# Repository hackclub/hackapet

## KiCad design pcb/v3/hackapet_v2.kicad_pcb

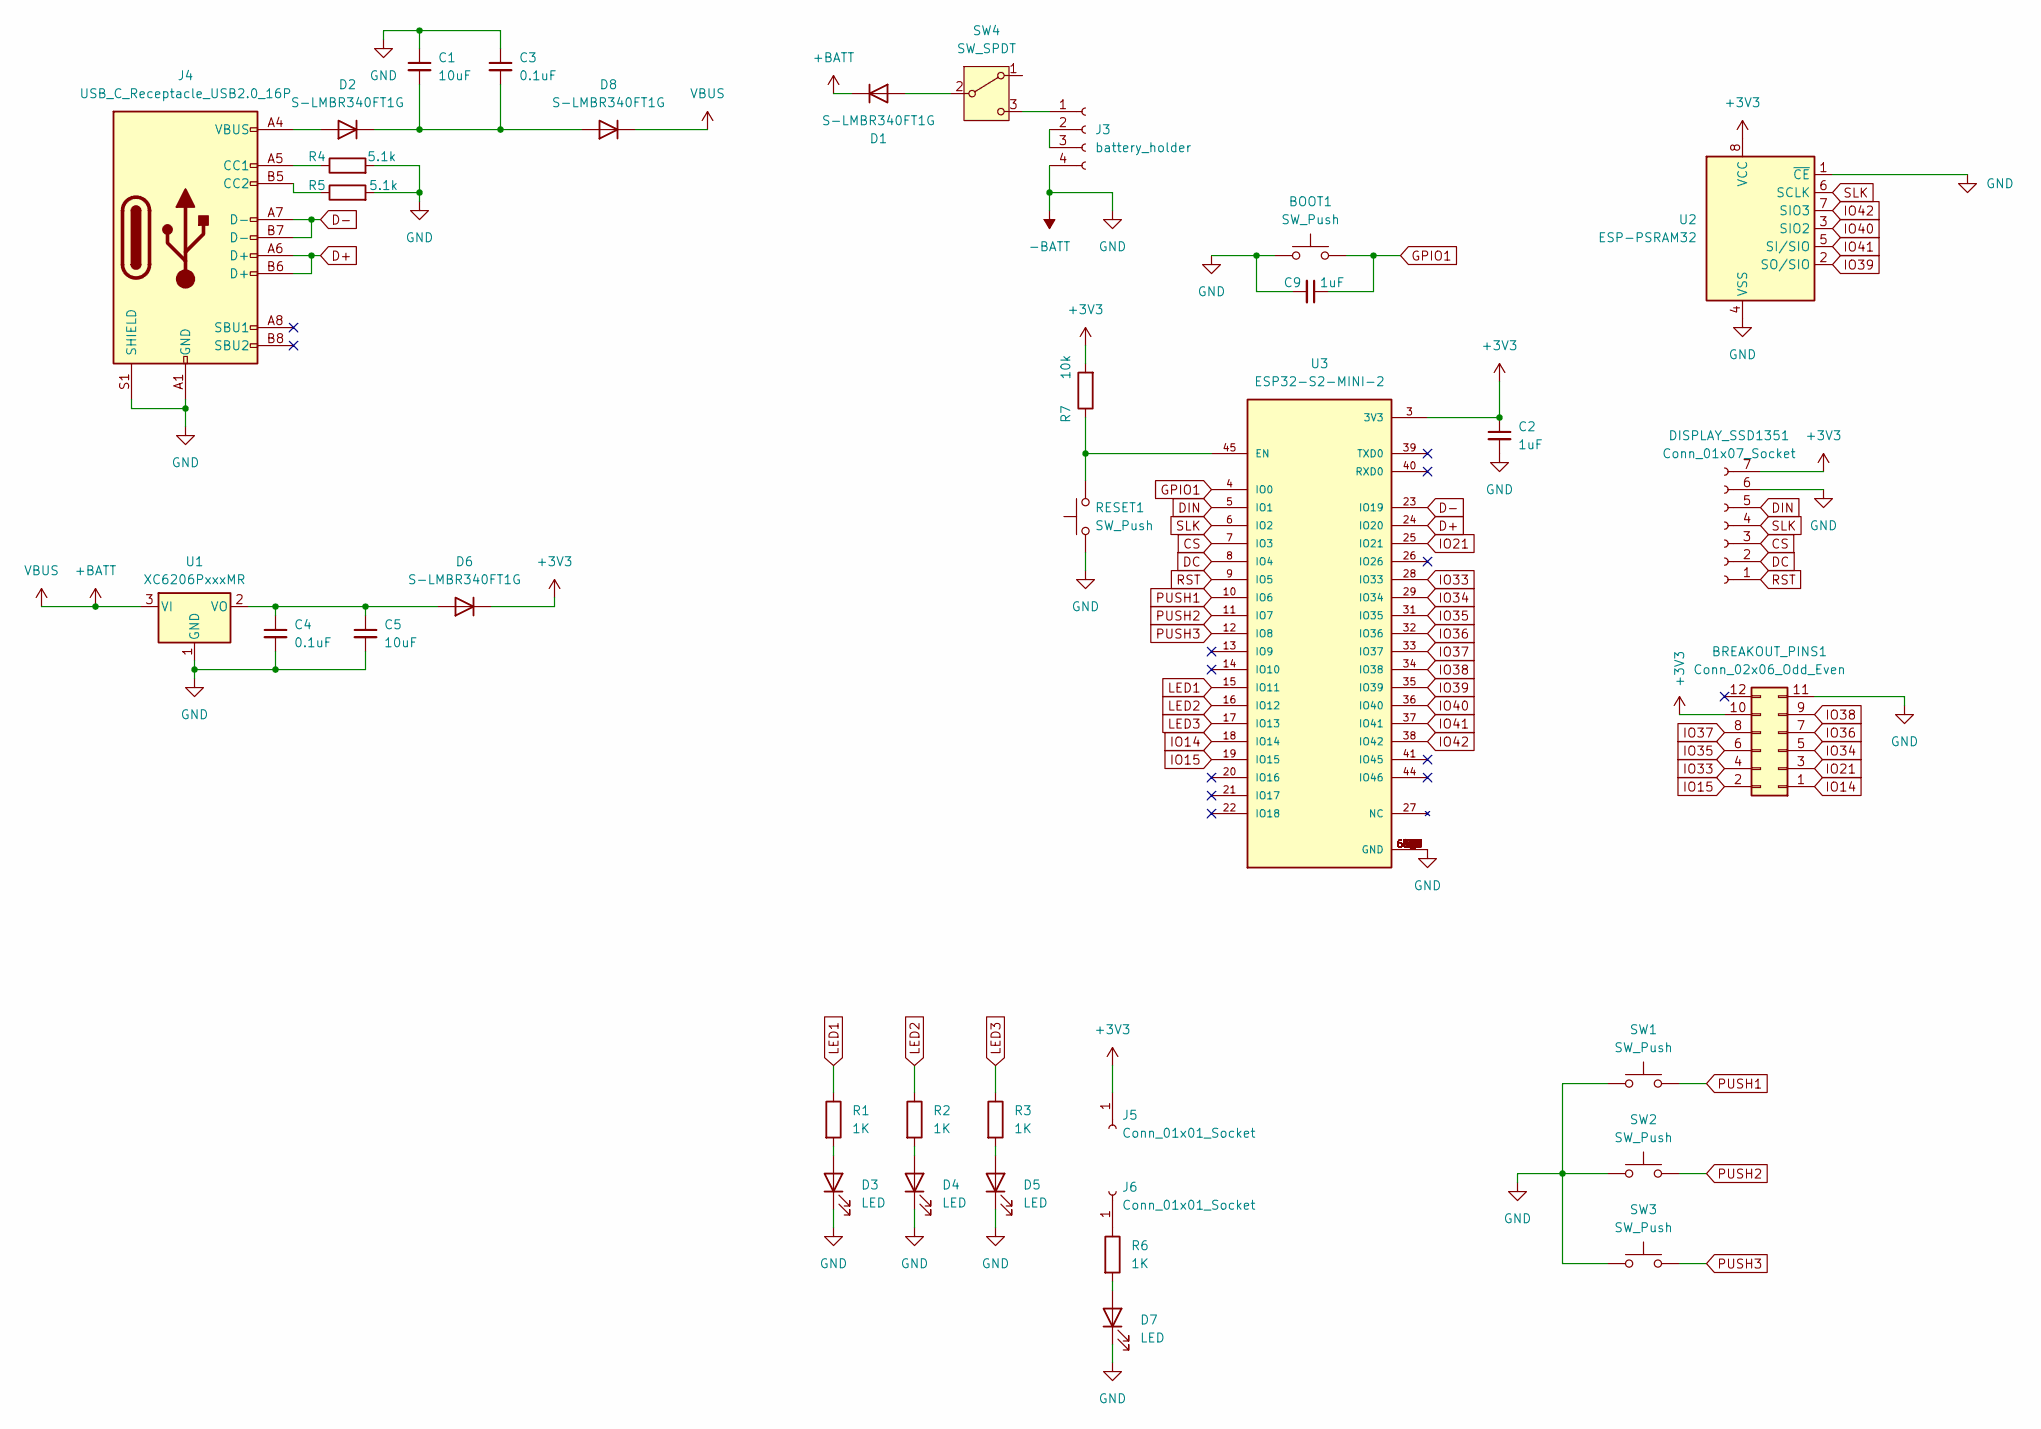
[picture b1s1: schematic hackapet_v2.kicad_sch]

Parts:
BOOT1: SW_Push; SW_Push_1P1T_XKB_TS-1187A; LCSC C381038
BREAKOUT_PINS1: Conn_02x06_Odd_Even
C1, C5: 10uF; C_0805_2012Metric; LCSC C5189822
C2, C9: 1uF; C_0805_2012Metric; LCSC C215803
C3, C4: 0.1uF; C_0805_2012Metric; LCSC C28378
D1, D2, D6, D8: S-LMBR340FT1G; D_0805_2012Metric; LCSC C2972823
D3, D4, D5, D7: LED; LED_0805_2012Metric
DISPLAY_SSD1351: Conn_01x07_Socket; PinSocket_1x07_P2.54mm_Vertical; LCSC C22438073
J3: battery_holder; 1022_batteryholder
J4: USB_C_Receptacle_USB2.0_16P; USB_C_Receptacle_HCTL_HC-TYPE-C-16P-01A; LCSC C393939
J5, J6: Conn_01x01_Socket; PinSocket_1x01_P2.54mm_Vertical
R1, R2, R3, R6: 1K; R_0805_2012Metric; LCSC C17513
R4, R5: 5.1k; R_0805_2012Metric; LCSC C104375
R7: 10k; R_0402_1005Metric
RESET1: SW_Push; SW_Push_1P1T_XKB_TS-1187A
SW1, SW2, SW3: SW_Push; SW_Push_1P1T_NO_6x6mm_H9.5mm; LCSC C381038
SW4: SW_SPDT; SW_DPDT_CK_JS202011JCQN; LCSC C221666
U1: XC6206PxxxMR; SOT-23-3
U2: ESP-PSRAM32; SOIC-8_3.9x4.9mm_P1.27mm
U3: ESP32-S2-MINI-2; XCVR_ESP32-S2-MINI-1; PARTREV 1.0; LCSC C3013906

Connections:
+3V3: BREAKOUT_PINS1.10, C2.1, D6.1 (K), DISPLAY_SSD1351.7, J5.1, R7.2, U2.8 (VCC), U3.3 (3V3)
+BATT: D1.1 (K), D8.1 (K), U1.3 (VI)
-BATT: BOOT1.1, BREAKOUT_PINS1.11, C1.1, C2.2, C3.1, C4.2, C5.2, C9.2, D3.1 (K), D4.1 (K), D5.1 (K), D7.1 (K), DISPLAY_SSD1351.6, J3.4, J4.A1 (GND), J4.A12 (GND), J4.B1 (GND), J4.B12 (GND), J4.S1 (SHIELD), R4.2, R5.2, RESET1.1, SW1.1, SW2.1, SW3.1, U1.1 (GND), U2.1 (~CE), U2.4 (VSS), U3.1 (GND), U3.2 (GND), U3.30 (GND), U3.42 (GND), U3.43 (GND), U3.46 (GND), U3.47 (GND), U3.48 (GND), U3.49 (GND), U3.50 (GND), U3.51 (GND), U3.52 (GND), U3.53 (GND), U3.54 (GND), U3.55 (GND), U3.56 (GND), U3.57 (GND), U3.58 (GND), U3.59 (GND), U3.60 (GND), U3.61 (GND), U3.61_1 (GND), U3.61_2 (GND), U3.61_3 (GND), U3.61_4 (GND), U3.61_5 (GND), U3.61_6 (GND), U3.61_7 (GND), U3.61_8 (GND), U3.62 (GND), U3.63 (GND), U3.64 (GND), U3.65 (GND)
CS: DISPLAY_SSD1351.3, U3.7 (IO3)
D+: J4.A6 (D+), J4.B6 (D+), U3.24 (IO20)
D-: J4.A7 (D-), J4.B7 (D-), U3.23 (IO19)
DC: DISPLAY_SSD1351.2, U3.8 (IO4)
DIN: DISPLAY_SSD1351.5, U3.5 (IO1)
GPIO1: BOOT1.2, C9.1, U3.4 (IO0)
IO14: BREAKOUT_PINS1.1, U3.18 (IO14)
IO15: BREAKOUT_PINS1.2, U3.19 (IO15)
IO21: BREAKOUT_PINS1.3, U3.25 (IO21)
IO33: BREAKOUT_PINS1.4, U3.28 (IO33)
IO34: BREAKOUT_PINS1.5, U3.29 (IO34)
IO35: BREAKOUT_PINS1.6, U3.31 (IO35)
IO36: BREAKOUT_PINS1.7, U3.32 (IO36)
IO37: BREAKOUT_PINS1.8, U3.33 (IO37)
IO38: BREAKOUT_PINS1.9, U3.34 (IO38)
IO39: U2.2 (SO/SIO), U3.35 (IO39)
IO40: U2.3 (SIO2), U3.36 (IO40)
IO41: U2.5 (SI/SIO), U3.37 (IO41)
IO42: U2.7 (SIO3), U3.38 (IO42)
LED1: R1.1, U3.15 (IO11)
LED2: R2.1, U3.16 (IO12)
LED3: R3.1, U3.17 (IO13)
unnamed: D1.2 (A), SW4.2 (B)
unnamed: D2.2 (A), J4.A4 (VBUS), J4.A9 (VBUS), J4.B4 (VBUS), J4.B9 (VBUS)
unnamed: C1.2, C3.2, D2.1 (K), D8.2 (A)
unnamed: D3.2 (A), R1.2
unnamed: D4.2 (A), R2.2
unnamed: D5.2 (A), R3.2
unnamed: C4.1, C5.1, D6.2 (A), U1.2 (VO)
unnamed: D7.2 (A), R6.2
unnamed: J3.1, SW4.3 (C)
unnamed: J3.2, J3.3
unnamed: J4.A5 (CC1), R4.1
unnamed: J4.B5 (CC2), R5.1
unnamed: J6.1, R6.1
unnamed: R7.1, RESET1.2, U3.45 (EN)
PUSH1: SW1.2, U3.10 (IO6)
PUSH2: SW2.2, U3.11 (IO7)
PUSH3: SW3.2, U3.12 (IO8)
RST: DISPLAY_SSD1351.1, U3.9 (IO5)
SLK: DISPLAY_SSD1351.4, U2.6 (SCLK), U3.6 (IO2)

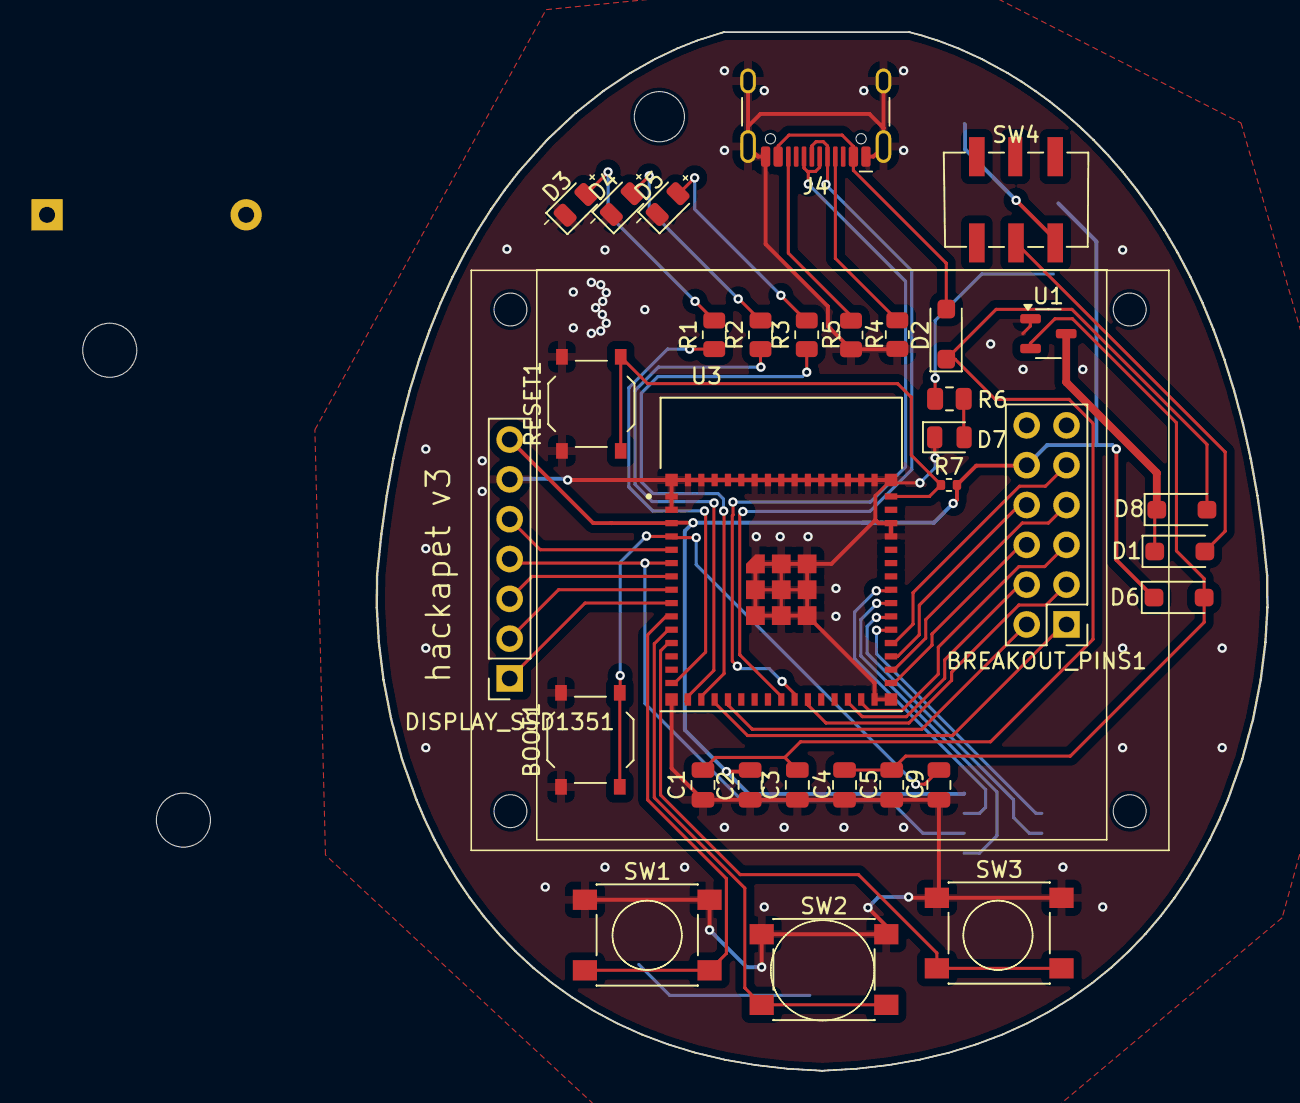
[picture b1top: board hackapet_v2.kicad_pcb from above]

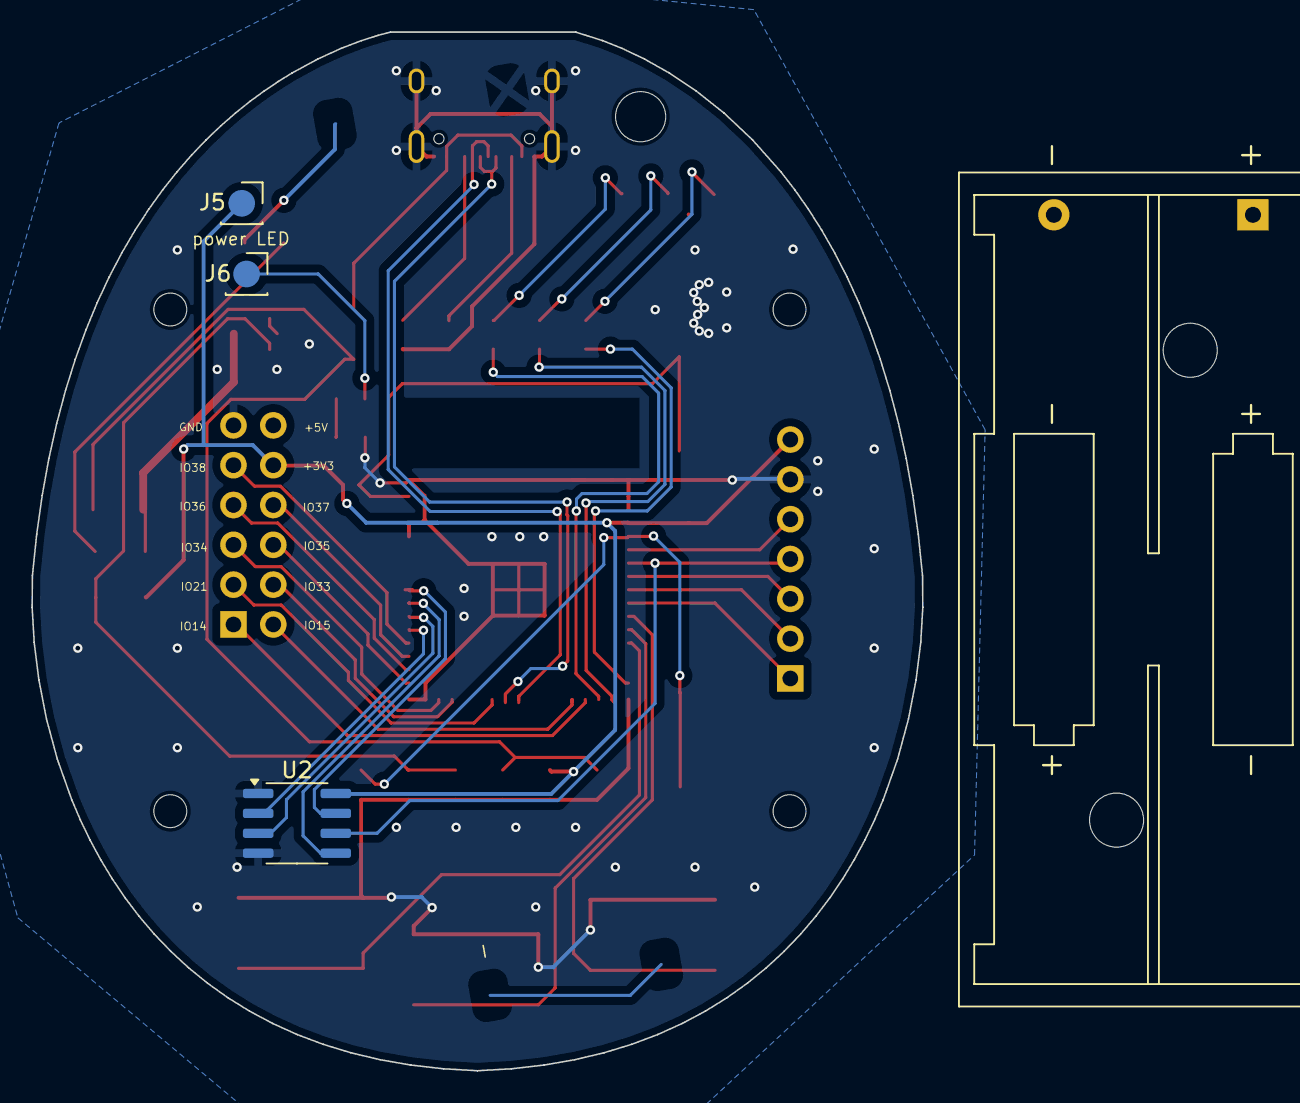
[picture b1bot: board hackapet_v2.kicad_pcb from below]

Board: 2 copper layers, 56.8 x 66.2 mm, 36 parts (4 on the bottom side), 43 nets.

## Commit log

2025-01-06 👻 boopet
2025-01-06 👻 boopet update 1
2025-01-11 feat: add my pet
2025-01-18 Added Escape The Rain! etr.srihari
2025-01-18 Update EmailButton.jsx to show email text
    Default email text color is white which makes it invisible when paired with the white bg.
2025-01-24 Adding monkey🐵
2025-01-24 adding monkey 🐵
2025-01-24 add requirments.txt
2025-01-27 ETR - UPDATE
2025-01-31 Made it work with circuit python
2025-02-01 I updated it again
2025-02-01 Added KawaiiPet
2025-02-02 starting
2025-02-02 i promise ill work more on it
2025-02-02 Create a
2025-02-02 added the main filesc lets see
2025-02-02 finished game !!!
2025-02-02 added game
2025-02-02 Create e
2025-02-03 Wizard pet - ian
    my hackapet submission
2025-02-03 new file: pets/NinjaRunner/Over.bmp new file: pets/NinjaRunner/ReadMe.md new file: pets/NinjaRunner/background.bmp new file: pets/NinjaRunner/background2.bmp new file: pets/NinjaRunner/cloud.bmp new 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
2025-02-03 Made a README
2025-02-03 Create code
2025-02-03 added my silly lil dino game
2025-02-04 space game :3
2025-02-04 silly dog eats things
    slack username - Nili
2025-02-04 wizard game
2025-02-04 added jack's adventure
    Niko slack username
2025-02-04 add cemetery crawler !
2025-02-04 add files
2025-02-04 remove pycache
2025-02-04 Add files via upload
    added some sprite changes and added idle animation + for jump
2025-02-04 just get rid of the text, adds more suspense to the game since you dont know if you are taking enough care or not
2025-02-05 hopefully good
2025-02-05 added README with button instructions
2025-02-06 silly dog eats things!
    i didn't upload the code to the right place at first lol - nili
2025-02-06 silly_dog
    i think this is it? i hope this works
2025-02-06 pls work
2025-02-08 VirtualPet
2025-02-09 Add files via upload
    god please let this work
2025-02-09 Add files via upload
    okay why do things keep on getting pulled out... this should be it?
2025-02-10 added aseprite file and made changes to the art to make it more distinct from the ref
2025-02-14 Revert "add my wys demake"
2025-02-15 final commit
2025-03-29 newest changes huge
2025-03-29 final huge big changes
